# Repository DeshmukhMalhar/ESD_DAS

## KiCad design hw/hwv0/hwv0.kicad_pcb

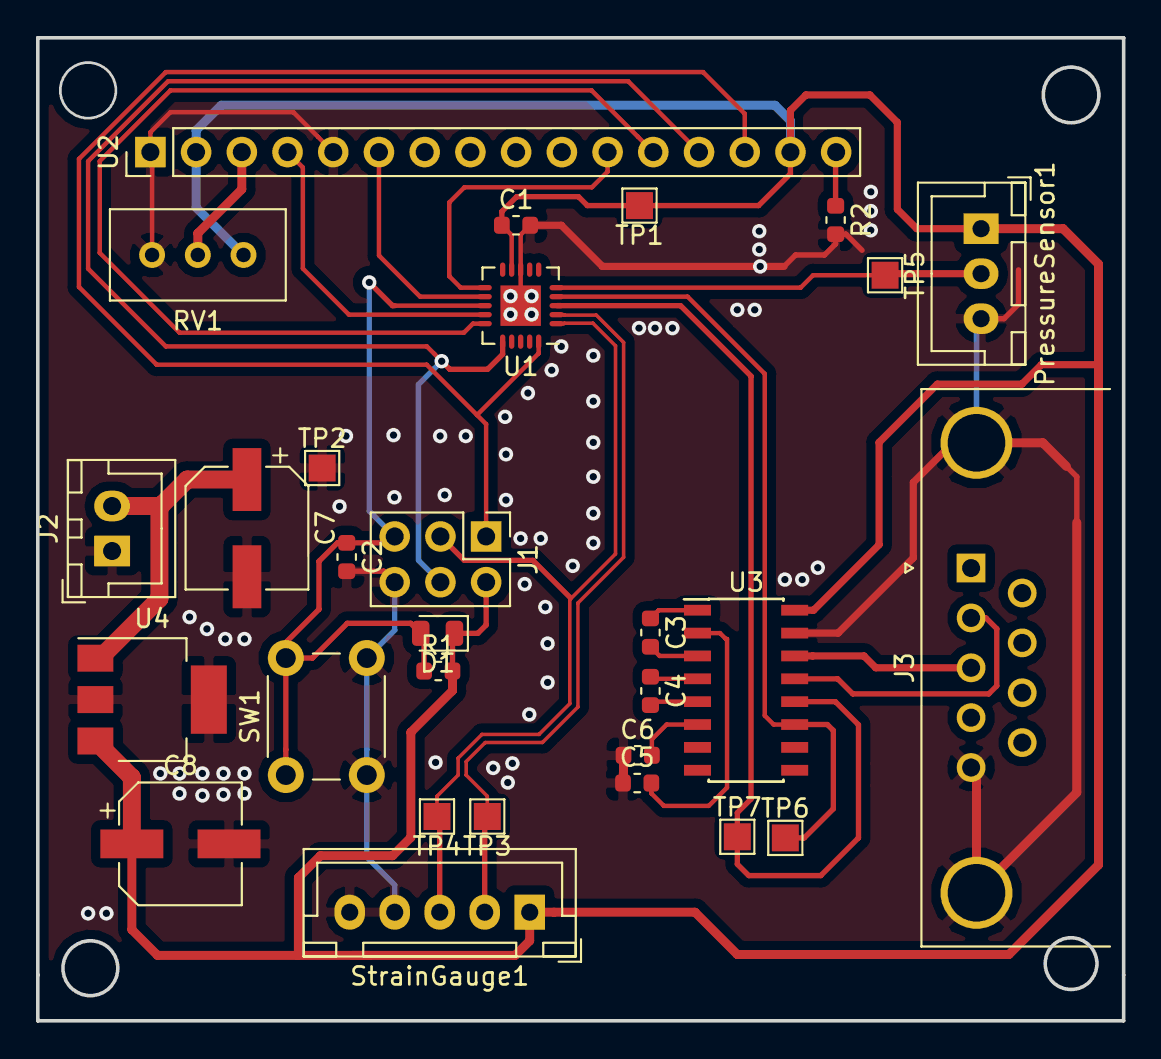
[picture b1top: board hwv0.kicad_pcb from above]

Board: 2 copper layers, 60.3 x 54.6 mm, 29 parts (0 on the bottom side), 25 nets.

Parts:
C1: C; C_0603_1608Metric
C2: 0u1; C_0603_1608Metric
C3, C4, C5, C6: 1u; C_0603_1608Metric
C7, C8: 10u; CP_Elec_6.3x3
D1: 1N4148; D_0805_2012Metric
J1: AVR-ISP-6; PinHeader_2x03_P2.54mm_Vertical
J2: PWR_IN_7-12V; JST_XH_B02B-XH-A_1x02_P2.50mm_Vertical
J3: RS232; DSUB-9_Female_Horizontal_P2.77x2.84mm_EdgePinOffset4.94mm_H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
PressureSensor1: Conn_01x03_Female; JST_XH_B03B-XH-A_1x03_P2.50mm_Vertical
R1: 10K; R_0603_1608Metric
R2: 270; R_0603_1608Metric
RV1: R_POT; Potentiometer_Bourns_3296W_Vertical
SW1: SW_Push; SW_PUSH_6mm
StrainGauge1: Conn_01x04_Shielded; JST_XH_B05B-XH-A_1x05_P2.50mm_Vertical
TP1: VCC; TestPoint_Pad_1.5x1.5mm
TP2: GND; TestPoint_Pad_1.5x1.5mm
TP3, TP4, TP5, TP6, TP7: TestPoint_Pad_1.5x1.5mm
U1: ATtiny84A-MU; QFN-20-1EP_4x4mm_P0.5mm_EP2.25x2.25mm
U2: LCD_1602; PinHeader_1x16_P2.54mm_Vertical
U3: MAX232I; SOIC-16_3.9x9.9mm_P1.27mm
U4: L7805; SOT-223-3_TabPin2

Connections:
+5V: C1.1, C8.1, D1.1, J1.2, PressureSensor1.1, R1.2, RV1.3, StrainGauge1.1, TP1.1, U1.9, U2.2, U2.15, U3.16, U4.3
/MISO: J1.1, U1.20, U2.14
/MOSI: J1.4, U1.16, U2.13
/P_sen_analogIN: PressureSensor1.2, TP5.1, U1.5
/RX_H: J3.2, U3.13
/RX_L: TP7.1, U1.3, U3.12
/SCK: J1.3, StrainGauge1.3, TP4.1, U1.1
/STRAINGAUGE+: StrainGauge1.2, TP3.1, U1.2
/TX_H: J3.3, U3.14
/TX_L: TP6.1, U1.4, U3.11
/~RST: C2.1, D1.2, J1.5, R1.1, SW1.1, U1.13
GNDD: C1.2, C2.2, C5.1, C6.1, C7.2, C8.2, J1.6, J2.1, J3.0, J3.5, PressureSensor1.3, R2.2, RV1.1, SW1.2, StrainGauge1.4, StrainGauge1.5, TP2.1, U1.8, U1.21, U2.1, U2.5, U3.15, U4.2
unnamed: C3.1, U3.1
unnamed: C3.2, U3.3
unnamed: C4.1, U3.4
unnamed: C4.2, U3.5
unnamed: C5.2, U3.2
unnamed: C6.2, U3.6
unnamed: C7.1, J2.2, U4.1
unnamed: R2.1, U2.16
unnamed: RV1.2, U2.3
unnamed: U1.11, U2.11
unnamed: U1.12, U2.6
unnamed: U1.14, U2.4
unnamed: U1.15, U2.12

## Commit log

2018-10-12 Yet to add sensors and ICSP connections
2018-10-12 Almost completed PCB
2018-10-13 finished PCB
2018-10-13 started adding documentation
2018-10-13 made schematic more clear
2018-10-17 stitched PCB
